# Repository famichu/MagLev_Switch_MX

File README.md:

# MagLev Switch MX

## Summary
These 3D printable switches have linear output hall effect sensors with magnetic levitation switches. The shape of this swich is compatable with the Cherry MX switch.

## Features
- Magnetic levitation axis
- Non-contact switch
- Linear output(adjustable actuation depth)
- Able to make with only 2 magnets and a hall sensor.
- Compatible shape with Cherry MX switch

## Structure
Most MagLev switches don't use hall effect sensors. I think this is because the magnetism is too strong or the distance from the magnet is too close to for the sensor to detect. Therefore I implemented with new method that by sandwiching the hall effect sensor between two magnets instead of using springs.

When the axis is pushed, the magnetism will cancel each other out, which causes the magnetism detected by hall effect sensor to become zero. This is how this switch works.
This method made the switch smaller, allowing it to have the same shape as existing switches.

## BOM
- PCB x1
- Hall effect sensor IC A1304 x1
- Pin header connector 1x1 x3
- 5mm diameter x 2mm height magnet x2
- Axis part(3D printerd) x1
- Botton part(3D printerd) x1
- Top part(3D printerd) x1
- Soldering jig(3D printed) x1(Optional)

### About the magnet and the hall effect sensor
The dimensions of the magnet used to make these models are 5mm diameter and 2mm thickness neodymium magnets. I used [this magnet](https://www.amazon.co.jp/gp/product/B08MJH42VK/).
The hall effect sensor I used is [A1304](https://www.allegromicro.com/~/media/Files/Datasheets/A1304-Datasheet.ashx) from Allegro MicroSystems.

## 3D Printing
I recommend to use SLA or DLP printer to print the body of the switches. And the recommended printing direction is the angle at which the groove is parallel to the platform.

## PCB
The PCB of this switch is manufactuable with single layer. But I recommend a load-bearing double layer PCB. 
Pins I used are the usual pinheaders. They're easy install with this Soldering Jig included in the repositry.

# Sample Numeric Keypad

## Features
- Used Maglev Switches
- Also useable with common Cherry MX switch types.
- This keypad has an LED indicator and a volume for changing the actuation depth.

## BOM
- PCB x1
- MagLev Switch MX x18
- Seeeduino Xiao x1
- Linear(B type) 10k Ohm Rotary potentiometers x1
- Broadcom LED bar graph HDSP-4850  x1
- Case bottom(3D printed) x1
- Case plate(3D printed) x1
- Case top(3D printed) x1
- Volume cap(3D printed) x1

### PCB
If you want to make the sample numeric keypad, **you'll need to download KiCAD libraries from [Seeed Wiki](https://wiki.seeedstudio.com/Seeeduino-XIAO/#resourses)**. 
Then put the "Seeeduino XIAO KICAD" directory and the "Seeeduino XIAO KICAD.pretty" directory under the "Sample_Numeric_Keypad\PCB" directory.

# Directory configuration
- **MagLevSwitch_MX**: Files for maglev switch units.
    - **Body**: 3D printable mesh files and the editable file with Fusion 360(F3Z).
    - **PCB**: KiCad project files and KiCad libraries with 3D models.
    - **SolderingJig**: 3D printable mesh files of soldering jig for the PCB of this switch.
- **Sample_Numeric_Keypad**
    - **Case**: 3D printable mesh files.
    - **Code**: Source codes for the key matrix controller(Seeeduino Xiao with ) and LED indicator(ATmega328P)
    - **PCB**: KiCad project files(**Libraries of Seeduino XIAO is not included.**).

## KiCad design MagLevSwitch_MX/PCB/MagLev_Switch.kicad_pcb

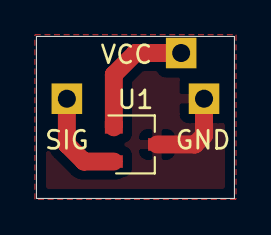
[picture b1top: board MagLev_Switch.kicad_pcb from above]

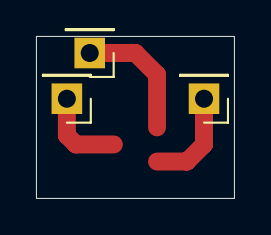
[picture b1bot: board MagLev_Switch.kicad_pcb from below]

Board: 2 copper layers, 11.0 x 9.0 mm, 4 parts (3 on the bottom side), 3 nets.

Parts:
GND: Conn_01x01; PinHeader_1x01_P2.54mm_Vertical
SIG: Conn_01x01; PinHeader_1x01_P2.54mm_Vertical
U1: A1302ELHLT-T; SOT-23W
VCC: Conn_01x01; PinHeader_1x01_P2.54mm_Vertical

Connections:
GND: GND.1, U1.3
unnamed: SIG.1, U1.2
VCC: U1.1, VCC.1

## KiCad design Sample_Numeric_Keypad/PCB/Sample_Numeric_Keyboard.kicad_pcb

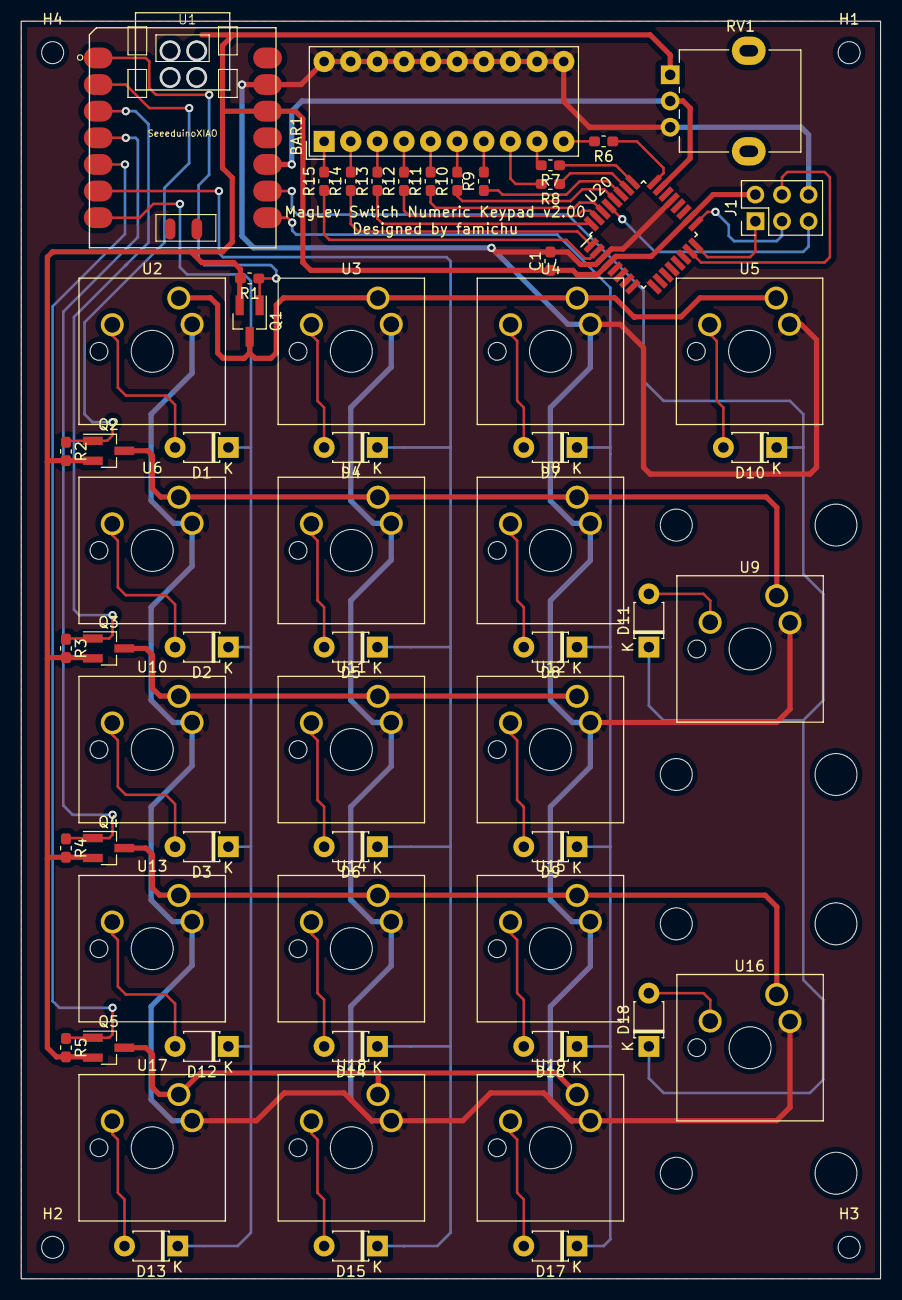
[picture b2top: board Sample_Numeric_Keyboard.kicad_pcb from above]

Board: 2 copper layers, 82.0 x 120.0 mm, 66 parts (0 on the bottom side), 59 nets.

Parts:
BAR1: HDSP-4850_2; HDSP-4850
C1: C; C_0603_1608Metric_Pad1.05x0.95mm_HandSolder
D1, D2, D3, D4, D5, D6, D7, D8, D9, D10, D11, D12, D13, D14, D15, D16, D17, D18: D; D_T-1_P5.08mm_Horizontal
H1, H2, H3, H4: MountingHole; MountingHole_2.1mm
J1: Conn_02x03_Odd_Even; PinHeader_2x03_P2.54mm_Vertical
Q1, Q2, Q3, Q4, Q5: Q_PMOS_GSD; SOT-23_Handsoldering
R1, R2, R3, R4, R5: 1k; R_0603_1608Metric_Pad1.05x0.95mm_HandSolder
R6, R7, R8, R9, R10, R11, R12, R13, R14, R15: 10; R_0603_1608Metric_Pad1.05x0.95mm_HandSolder
RV1: R_POT; Potentiometer_Alpha_RD901F-40-00D_Single_Vertical
U1: SeeeduinoXIAO; Seeeduino XIAO-MOUDLE
U2, U3, U4, U5, U6, U7, U8, U10, U11, U12, U13, U14, U15, U17, U18, U19: MagLevSwitch; SW_MagLev_1.00u_PCB
U9, U16: MagLevSwitch; SW_MagLev_2.00u_Vertical_PCB
U20: ATmega328-AU; TQFP-32_7x7mm_P0.8mm

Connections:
+3V3: C1.1, J1.2, Q1.2, Q2.2, Q3.2, Q4.2, Q5.2, R1.2, R2.2, R3.2, R4.2, R5.2, RV1.1, U1.12, U20.4, U20.6, U20.18
/COL_0: D1.1, D2.1, D3.1, D12.1, D13.1, U1.7
/COL_1: D4.1, D5.1, D6.1, D14.1, D15.1, U1.6
/COL_2: D7.1, D8.1, D9.1, D16.1, D17.1, U1.8
/COL_3: D10.1, D11.1, D18.1, U1.9
/MISO: J1.1, U20.16
/MOSI: J1.4, U20.15
/ROW_0: Q1.1, R1.1, U1.1
/ROW_1: Q2.1, R2.1, U1.2
/ROW_2: Q3.1, R3.1, U1.3
/ROW_3: Q4.1, R4.1, U1.4
/ROW_4: Q5.1, R5.1, U1.5
/RST: J1.5, U20.29
/SCK: J1.3, U20.17
/VOL: RV1.2, U1.10, U20.23
GND: BAR1.11, BAR1.12, BAR1.13, BAR1.14, BAR1.15, BAR1.16, BAR1.17, BAR1.18, BAR1.19, BAR1.20, C1.2, J1.6, RV1.3, U1.13, U2.3, U3.3, U4.3, U5.3, U6.3, U7.3, U8.3, U9.3, U10.3, U11.3, U12.3, U13.3, U14.3, U15.3, U16.3, U17.3, U18.3, U19.3, U20.3, U20.5, U20.21
unnamed: BAR1.1, R15.2
unnamed: BAR1.2, R14.2
unnamed: BAR1.3, R13.2
unnamed: BAR1.4, R12.2
unnamed: BAR1.5, R11.2
unnamed: BAR1.6, R10.2
unnamed: BAR1.7, R9.2
unnamed: BAR1.8, R8.2
unnamed: BAR1.9, R7.2
unnamed: BAR1.10, R6.2
unnamed: D1.2, U2.2
unnamed: D2.2, U6.2
unnamed: D3.2, U10.2
unnamed: D4.2, U3.2
unnamed: D5.2, U7.2
unnamed: D6.2, U11.2
unnamed: D7.2, U4.2
unnamed: D8.2, U8.2
unnamed: D9.2, U12.2
unnamed: D10.2, U5.2
unnamed: D11.2, U9.2
unnamed: D12.2, U13.2
unnamed: D13.2, U17.2
unnamed: D14.2, U14.2
unnamed: D15.2, U18.2
unnamed: D16.2, U15.2
unnamed: D17.2, U19.2
unnamed: D18.2, U16.2
unnamed: Q1.3, U2.1, U3.1, U4.1, U5.1
unnamed: Q2.3, U6.1, U7.1, U8.1, U9.1
unnamed: Q3.3, U10.1, U11.1, U12.1
unnamed: Q4.3, U13.1, U14.1, U15.1, U16.1
unnamed: Q5.3, U17.1, U18.1, U19.1
unnamed: R6.1, U20.24
unnamed: R7.1, U20.25
unnamed: R8.1, U20.26
unnamed: R9.1, U20.27
unnamed: R10.1, U20.28
unnamed: R11.1, U20.30
unnamed: R12.1, U20.31
unnamed: R13.1, U20.32
unnamed: R14.1, U20.1
unnamed: R15.1, U20.2

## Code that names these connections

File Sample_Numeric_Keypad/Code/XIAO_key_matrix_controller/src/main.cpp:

#include <Arduino.h>
#include <TimerTC3.h>
#include <TinyUSB_Mouse_and_Keyboard.h>

#include <key_switch.cpp>
#include <fet.cpp>

// Pins for row of the matrix
#define PIN_ROW_0 0
#define PIN_ROW_1 1
#define PIN_ROW_2 2
#define PIN_ROW_3 3
#define PIN_ROW_4 4

// Pins for col of the matrix
#define PIN_COL_0 A6
#define PIN_COL_1 A5
#define PIN_COL_2 A7
#define PIN_COL_3 A8

// A pin for actuation depth volume
#define PIN_VOL A9

const u_int16_t PULSE_FREQ = 50;     // Frequency for scanning the state of swiches
const u_int16_t LOWER_LIMIT = 300;   // Lower limit of the actuation depth
const u_int16_t UPPER_LIMIT = 900;   // Upper limit of the actuation depth

const u_int8_t G_ROW_PINS[]   = {PIN_ROW_0, PIN_ROW_1, PIN_ROW_2, PIN_ROW_3, PIN_ROW_4};    // Pins connected to FETs
const u_int8_t G_COL_PINS[]   = {PIN_COL_0, PIN_COL_1, PIN_COL_2, PIN_COL_3};               // Pins connected to Key switches

// Keycode map for each key
char G_KEY_CODES[5][4] = {
    {0xB2, '/', '*', '-'}, 
    {'7', '8', '9', 0x6B}, 
    {'4', '5', '6', ' '}, 
    {'1', '2', '3', 0xB0}, 
    {'0', '0', '.', ' '}
};

KeySwitch G_KEY_SWITCHES[sizeof(G_ROW_PINS)][sizeof(G_COL_PINS)]; // KeySwitch Object
FET G_FETS[sizeof(G_ROW_PINS)]; // FET Object

int actuation_depth; // Global variable to put actuation depth.

// Prototypes
int updateActuationDepth();
void updateState();


void setup() {
    // Get initial actuation depth and begin Keyboard.
    actuation_depth = updateActuationDepth();
    Keyboard.begin();

    // Make instances of key switches.
    for(u_int8_t row = 0; row < sizeof(G_ROW_PINS); row++){
        G_FETS[row] = FET(G_ROW_PINS[row], true);
        for(u_int8_t col = 0; col < sizeof(G_COL_PINS); col++){
            G_KEY_SWITCHES[row][col] = KeySwitch(G_COL_PINS[col], G_KEY_CODES[row][col], false, true, &actuation_depth);
        }
    }

    // Set timer interrupt
    TimerTc3.initialize(1000000 / (PULSE_FREQ * sizeof(G_ROW_PINS) * 4));
    TimerTc3.attachInterrupt(updateState);
}

void loop() {
    // Nothing to do in loop method.
    // Codes are working only by timer interrupt.
}


// Update actuation depth set with volume.
int updateActuationDepth(){
    int result = max(LOWER_LIMIT, analogRead(PIN_VOL));
    result = min(result, UPPER_LIMIT);

    return result;    
}


// Update switches status. This method are called only by timer interrupt.
void updateState(){
    static size_t row = 0;
    static u_int8_t off_count = 0;
    actuation_depth = updateActuationDepth();

    if(row >= sizeof(G_ROW_PINS)){
        row = 0;
    }
    if(G_FETS[row].is_on()){
        for(size_t col = 0; col < sizeof(G_COL_PINS); col++){
            G_KEY_SWITCHES[row][col].UpdateState();

            if((row == 4) && (col == 1)){
                if(G_KEY_SWITCHES[row][col].IsPushed() && !G_KEY_SWITCHES[row][col].IsLongPushed()){
                    Keyboard.print("00");
                }
            }
            else if((row == 0) && (col == 2)){
                if(G_KEY_SWITCHES[row][col].IsPushed()){
                    Keyboard.press(0x85);
                    Keyboard.press('8');
                }
                else if(G_KEY_SWITCHES[row][col].IsReleased()){
                    Keyboard.release(0x85);
                    Keyboard.release('8');
                }
            }
            else if((row == 1) && (col == 3)){
                if(G_KEY_SWITCHES[row][col].IsPushed()){
                    Keyboard.press(0x85);
                    Keyboard.press('=');
                }
                else if(G_KEY_SWITCHES[row][col].IsReleased()){
                    Keyboard.release(0x85);
                    Keyboard.release('=');
                }
            }
            else{
                if(G_KEY_SWITCHES[row][col].IsPushed()){
                    Keyboard.press(G_KEY_SWITCHES[row][col].Keycode());
                }
                else if(G_KEY_SWITCHES[row][col].IsReleased()){
                    Keyboard.release(G_KEY_SWITCHES[row][col].Keycode());
                }
            }
        }
        G_FETS[row].output(false);
        row++;
    }
    else{
        off_count++;
        if(off_count >= 3){
            off_count =  0;
            G_FETS[row].output(true);
        }
    }
}

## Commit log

2021-12-05 publish the maglev switch and sample numeric keypad
2022-01-30 Add images
2022-02-01 Add "Features", "BOM", "Structure" items.
2022-02-14 Update the axis shape
    Changing the axis shape to reduce the frictional resistance between axis and body.
2023-06-04 Fix code, change LICENSE and silk of PCB
2023-06-04 Fix LICENSE
2023-10-06 Update README.md
    英語訳をもうちょっと自然な方にしますた！
    多分これで英語を読む方でももう少し読みやすくなると思います！
    Changed English translation to a more natural one. It should prolly make it more easy to read than b4. GG!
